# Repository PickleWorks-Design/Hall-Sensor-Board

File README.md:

# Hall-Sensor-Board

This board is for anyone who has a motor with a busted hall sensor board that needs fixing

Manufacturing has been set up for JLCPCB assembly service

Required files are included in the production folder

jlcpcb
gerber -> hall_sensor_board.zip

materials -> bom.csv

placement -> positions.csv

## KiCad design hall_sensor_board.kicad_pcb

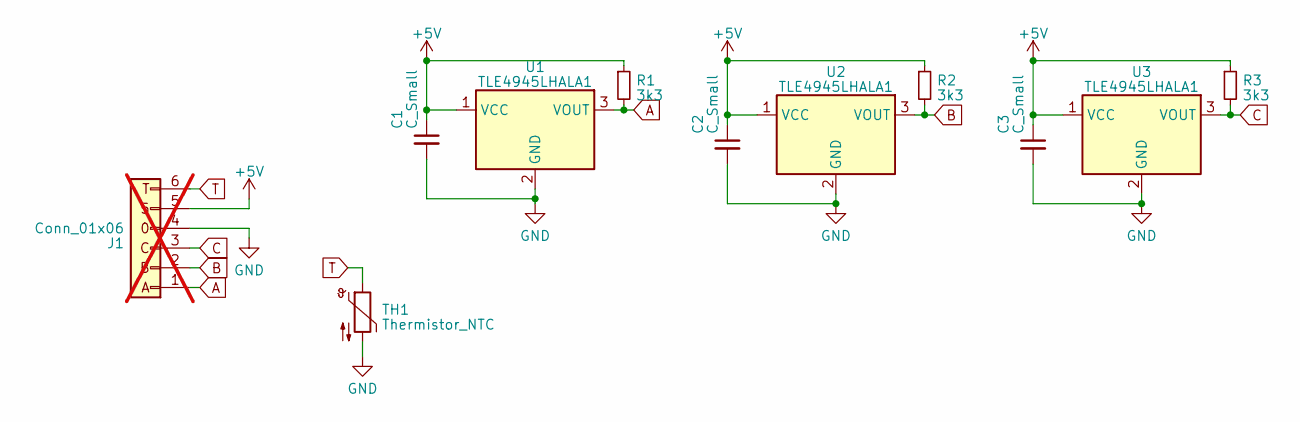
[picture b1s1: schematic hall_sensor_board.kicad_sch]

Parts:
C1, C2, C3: C_Small; C_0603_1608Metric; LCSC C53987
J1: Conn_01x06; hall_connector; not fitted
R1, R2, R3: 3k3; R_0603_1608Metric; LCSC C22978
TH1: Thermistor_NTC; C_0603_1608Metric; LCSC C338606
U1, U2, U3: TLE4945LHALA1

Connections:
+5V: C1.1, C2.1, C3.1, J1.5, R1.1, R2.1, R3.1, U1.1 (VCC), U2.1 (VCC), U3.1 (VCC)
A: J1.1, R1.2, U1.3 (VOUT)
B: J1.2, R2.2, U2.3 (VOUT)
C: J1.3, R3.2, U3.3 (VOUT)
GND: C1.2, C2.2, C3.2, J1.4, TH1.2, U1.2 (GND), U2.2 (GND), U3.2 (GND)
T: J1.6, TH1.1

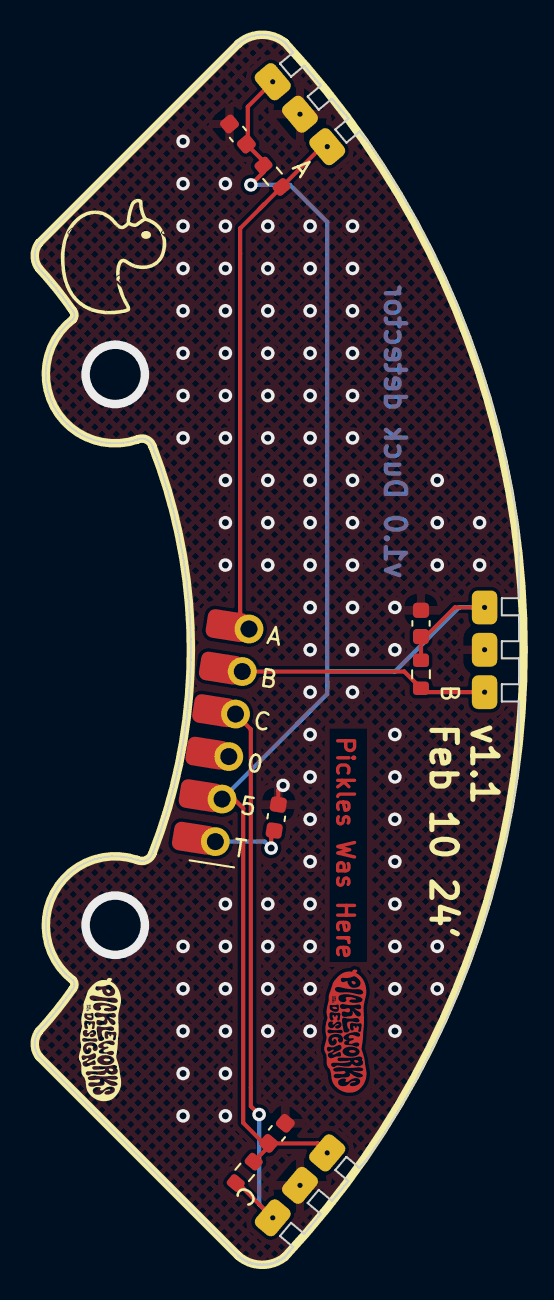
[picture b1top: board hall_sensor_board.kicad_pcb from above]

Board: 2 copper layers, 28.5 x 72.6 mm, 11 parts (0 on the bottom side), 6 nets.

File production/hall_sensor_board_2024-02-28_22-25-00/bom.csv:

Designator,Footprint,Quantity,Value,LCSC Part #
,af4c8d2e-6e3c-4016-b70e-df9501a44249,1,,
"C1, C2, C3",0603,3,C_Small,C53987
J1,hall_connector,1,Conn_01x06,DNP
"R1, R2, R3",0603,3,3k3,C22978
TH1,0603,1,Thermistor_NTC,C338606
"U1, U2, U3",TLE4945LHALA1,3,TLE4945LHALA1,

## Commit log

2024-10-27 tracking file additons, added production files
